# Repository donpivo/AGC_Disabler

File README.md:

Description: https://retronics.no/2024/05/04/diy-agc-disabler-for-use-when-aligning-vacuum-tube-radios/

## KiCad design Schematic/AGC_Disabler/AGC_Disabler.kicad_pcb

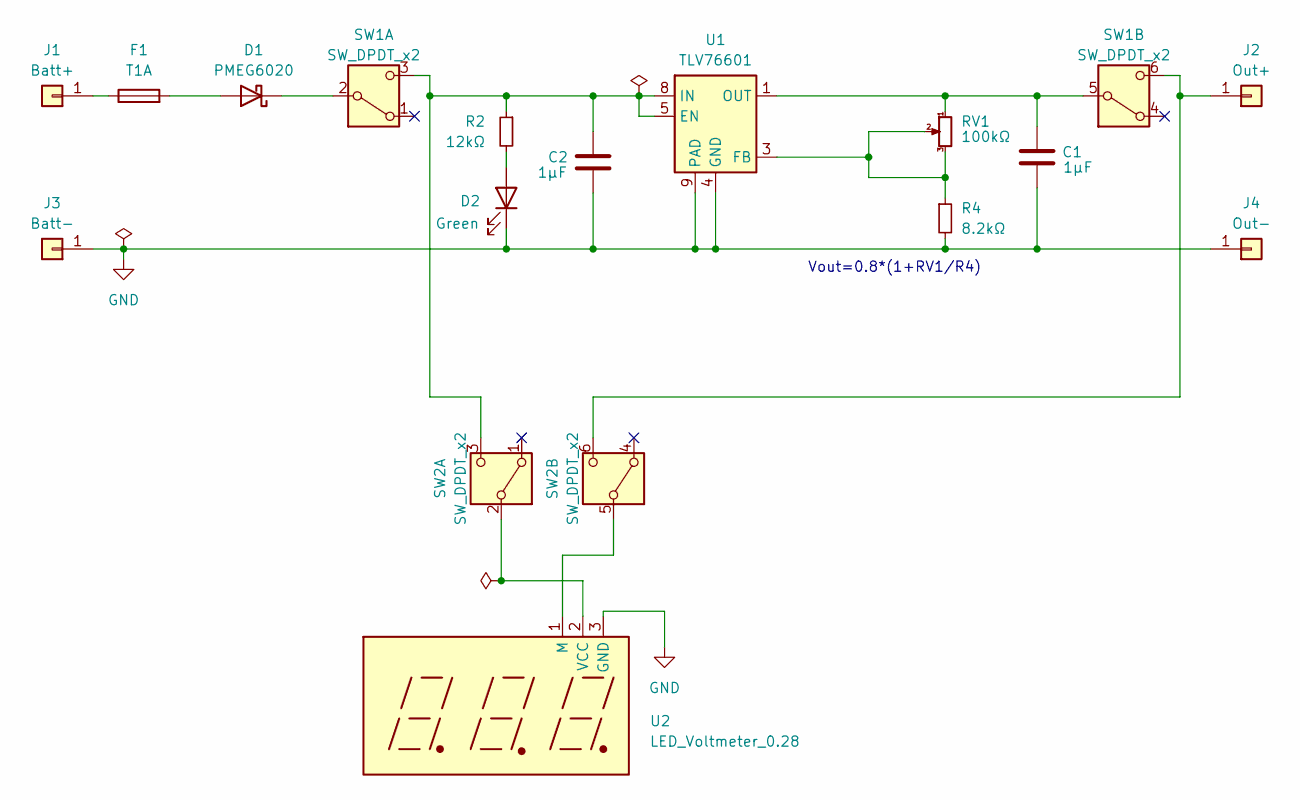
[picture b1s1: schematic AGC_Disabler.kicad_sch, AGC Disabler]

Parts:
C1, C2: 1µF; C_0603_1608Metric_Pad1.08x0.95mm_HandSolder
D1: PMEG6020; Nexperia_CFP3_SOD-123W
D2: Green; LED_0603_1608Metric_Pad1.05x0.95mm_HandSolder
F1: T1A; Fuse_1206_3216Metric_Pad1.42x1.75mm_HandSolder
J1: Batt+; TestPoint_Pad_D2.5mm
J2: Out+; TestPoint_Pad_D2.5mm
J3: Batt-; TestPoint_Pad_D2.5mm
J4: Out-; TestPoint_Pad_D2.5mm
R2: 12kΩ; R_0603_1608Metric_Pad0.98x0.95mm_HandSolder
R4: 8.2kΩ; R_0603_1608Metric_Pad0.98x0.95mm_HandSolder
RV1: 100kΩ; Potentiometer_Bourns_3386P_Vertical
SW1: SW_DPDT_x2; CUS22TB
SW2: SW_DPDT_x2
U1: TLV76601; TLV76601QWDRBRQ1
U2: LED_Voltmeter_0.28

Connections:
GND: C1.2, C2.2, D2.1 (K), J3.1, J4.1, R4.2, U1.4 (GND), U1.6 (GND), U1.9 (PAD), U2.3 (GND)
unnamed: D1.2 (A), F1.2
unnamed: D1.1 (K), SW1.2 (B)
unnamed: D2.2 (A), R2.2
unnamed: F1.1, J1.1
unnamed: J2.1, SW1.6 (C), SW2.6 (C)
unnamed: C2.1, R2.1, SW1.3 (C), SW2.3 (C), U1.5 (EN), U1.8 (IN)
unnamed: C1.1, RV1.1, SW1.5 (B), U1.1 (OUT)
unnamed: SW2.2 (B), U2.2 (VCC)
unnamed: SW2.5 (B), U2.1 (M)
unnamed: R4.1, RV1.2, RV1.3, U1.3 (FB)

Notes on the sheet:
Vout=0.8*(1+RV1/R4)

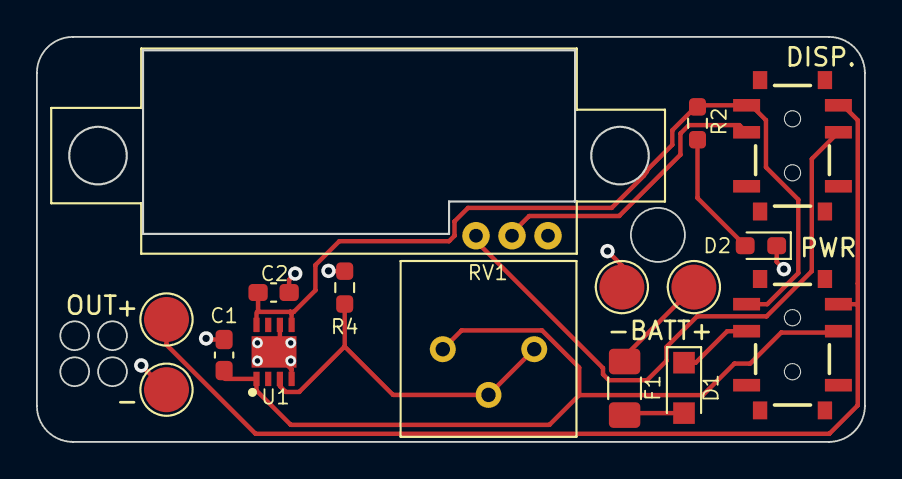
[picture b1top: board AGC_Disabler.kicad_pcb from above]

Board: 2 copper layers, 46.0 x 22.5 mm, 16 parts (0 on the bottom side), 11 nets.

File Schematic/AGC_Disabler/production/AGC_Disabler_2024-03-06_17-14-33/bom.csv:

Designator,Footprint,Quantity,Value,LCSC Part #
"C1, C2",0603,2,1µF,
D1,Nexperia_CFP3_SOD-123W,1,PMEG6020,
D2,0603,1,Green,
F1,1206,1,T1A,
J1,TestPoint_Pad_D2.5mm,1,Batt+,
J2,TestPoint_Pad_D2.5mm,1,Out+,
J3,TestPoint_Pad_D2.5mm,1,Batt-,
J4,TestPoint_Pad_D2.5mm,1,Out-,
R1,0603,1,0Ω,DNP
R2,0603,1,12kΩ,
R3,0603,1,0Ω,
R4,0603,1,8.2kΩ,
RV1,Potentiometer_Bourns_3386P_Vertical,1,100kΩ,
"SW1, SW2",CUS22TB,2,SW_DPDT_x2,
U1,TLV76601QWDRBRQ1,1,TLV76601,
U2,LED_Voltmeter_0.28,1,LED_Voltmeter_0.28,

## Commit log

2024-03-08 New regulator IC: TLV76601. Rearranged PCB layout.
2024-05-04 File cleanup
